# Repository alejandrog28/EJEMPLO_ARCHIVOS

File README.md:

# EJEMPLO_ARCHIVOS
Este es un ejemplo de como subir archivos a este repositorio remoto.

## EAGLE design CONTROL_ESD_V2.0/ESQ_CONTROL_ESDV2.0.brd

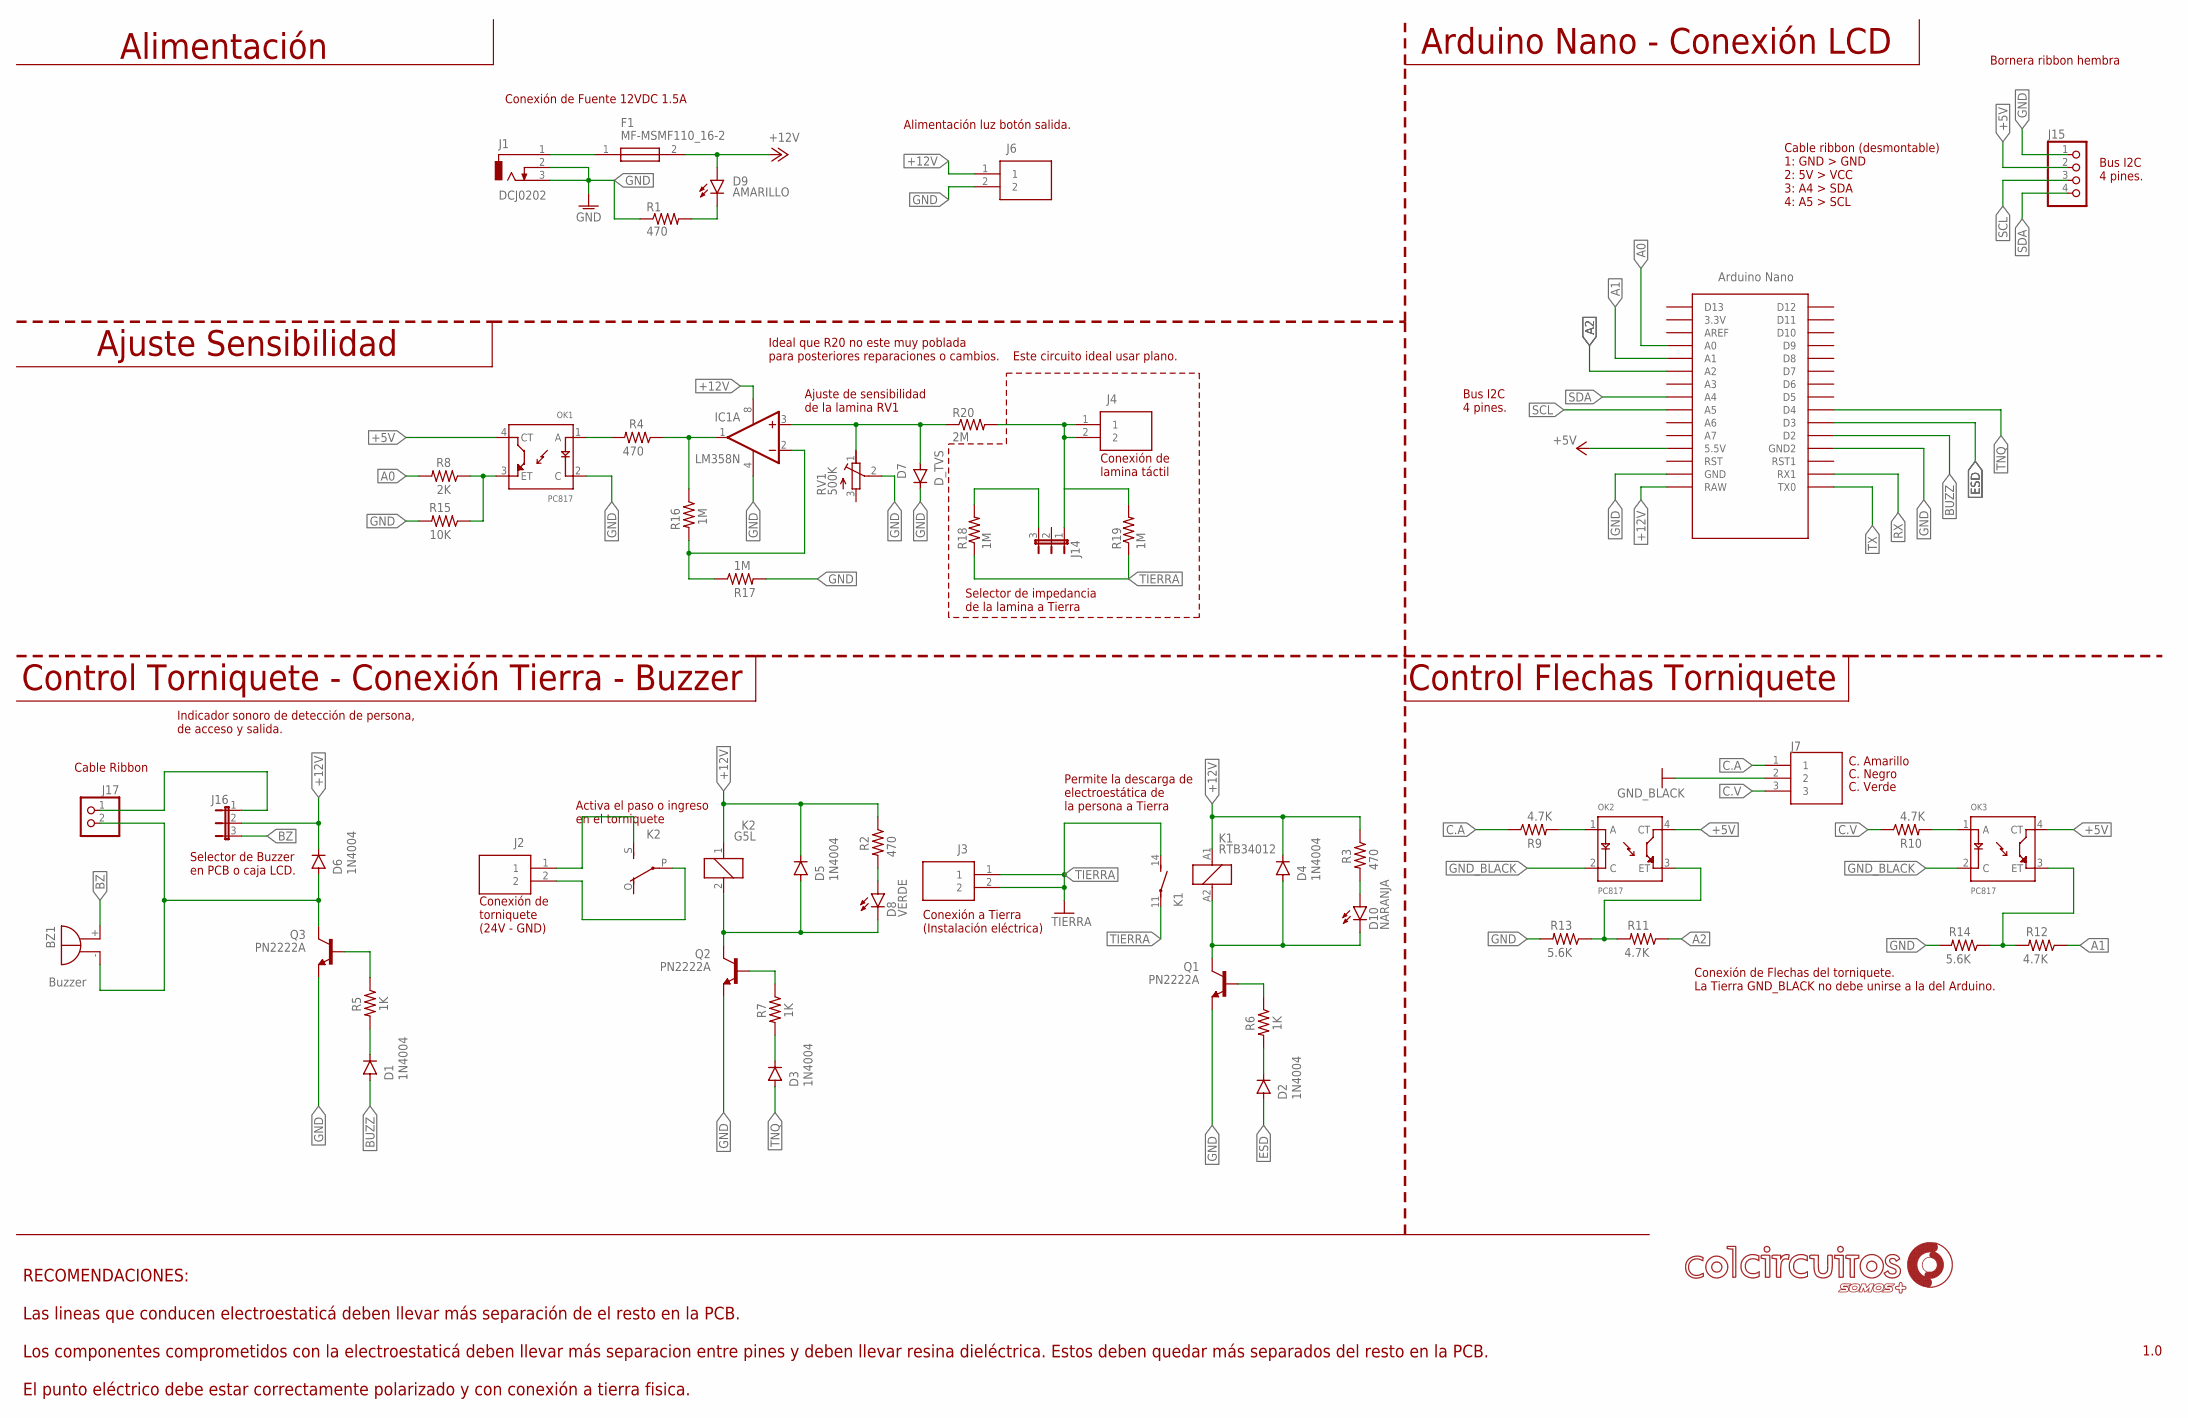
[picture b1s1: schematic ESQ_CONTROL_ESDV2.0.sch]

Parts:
BZ1: Buzzer; EB2209A
D1, D2, D3, D4, D5, D6: 1N4004; DO41-10
D7: D_TVS; DO214AC
D8: VERDE; LED5MM
D9: AMARILLO; LED5MM
D10: NARANJA; LED5MM
F1: MF-MSMF110_16-2; FUSC4632X85N
IC1: LM358N; DIL08
J1: DCJ0202
J2, J3, J4, J6: 20020107-H021A01LF; SHDR2W100P0X508_1X2_1216X850X1
J7: 691311500103; SHDR3W100P0X508_1X3_1724X850X1
J14, J16: JP2E; JP2
J15: PINHD-1X4; 1X04
J17: PINHD-1X2; 1X02
K1: RTB34012; RT-N/O12A3.5
K2: G5L; G5LE
OK1, OK2, OK3: PC817; SOT254P975X400-4N
Q1, Q2, Q3: PN2222A; TO92
R1, R2, R3, R4: 470; R0805
R5, R6, R7: 1K; R0805
R8: 2K; R0805
R9, R10, R11, R12: 4.7K; R0805
R13, R14: 5.6K; R0805
R15: 10K; R0805
R16, R17: 1M; R0805
R18, R19: 1M; R1210
R20: 2M; R1210
RV1: 500K; RTRIMT93YA
U$1: NANO

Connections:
+5V: J15.2, OK1.4 (CT), OK2.4 (CT), OK3.4 (CT), U$1.5V (5.5V)
+12V: D4.C, D5.C, D6.C, D9.A, F1.2, IC1.8 (V+), J6.1, J16.2, K1.A1 (1), K2.1, R2.1, R3.1, U$1.RAW
A0: R8.2, U$1.A0
A1: R12.1, U$1.A1
A2: R11.1, U$1.A2
BUZZ: D1.A, U$1.D2
BZ: BZ1.+, J16.3
C.A: J7.1, R9.1
C.V: J7.3, R10.1
ESD: D2.A, U$1.D3
GND: D7.C, IC1.4 (V-), J1.2, J1.3, J6.2, J15.1, OK1.2 (C), Q1.1 (E), Q2.1 (E), Q3.1 (E), R1.1, R13.2, R14.2, R15.2, R17.2, RV1.2 (S), U$1.GND, U$1.GND1 (GND2)
GND_BLACK: J7.2, OK2.2 (C), OK3.2 (C)
unnamed: OK1.3 (ET), R8.1, R15.1
unnamed: OK1.1 (A), R4.2
unnamed: IC1.2 (-IN), R16.2, R17.1
unnamed: IC1.1 (OUT), R4.1, R16.1
unnamed: D7.A, IC1.3 (+IN), R20.1, RV1.1 (E)
unnamed: J14.3, R18.2
unnamed: BZ1.-, D6.A, J17.2, Q3.3 (C)
unnamed: F1.1, J1.1
unnamed: J16.1, J17.1
unnamed: D9.K (C), R1.2
unnamed: J2.1, K2.S
unnamed: D5.A, D8.K (C), K2.2, Q2.3 (C)
unnamed: J2.2, K2.P
unnamed: D8.A, R2.2
unnamed: D3.C, R7.2
unnamed: Q2.2 (B), R7.1
unnamed: D4.A, D10.K (C), K1.A2 (2), Q1.3 (C)
unnamed: D2.C, R6.2
unnamed: Q1.2 (B), R6.1
unnamed: OK2.1 (A), R9.2
unnamed: OK2.3 (ET), R11.2, R13.1
unnamed: OK3.3 (ET), R12.2, R14.1
unnamed: D10.A, R3.2
unnamed: OK3.1 (A), R10.2
unnamed: J4.1, J4.2, J14.1, R19.2, R20.2
unnamed: Q3.2 (B), R5.1
unnamed: D1.C, R5.2
RX: U$1.RX1
SCL: J15.3, U$1.A5
SDA: J15.4, U$1.A4
TIERRA: J3.1, J3.2, K1.11, K1.14 (S), R18.1, R19.1
TNQ: D3.A, U$1.D4
TX: U$1.TX0

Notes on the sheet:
Ajuste de sensibilidad de la lamina RV1
Conexión de lamina táctil
Selector de impedancia de la lamina a Tierra
Activa el paso o ingreso en el torniquete
Conexión de torniquete (24V - GND)
Permite la descarga de electroestática de la persona a Tierra
Conexión a Tierra (Instalación eléctrica)
C. Amarillo
C. Negro
C. Verde
Conexión de Flechas del torniquete. La Tierra GND_BLACK no debe unirse a la del Arduino.
Alimentación
Ajuste Sensibilidad
Control Flechas Torniquete
Control Torniquete - Conexión Tierra - Buzzer
Arduino Nano - Conexión LCD
Cable ribbon (desmontable) 1: GND > GND 2: 5V > VCC 3: A4 > SDA 4: A5 > SCL
Bus I2C 4 pines.
RECOMENDACIONES: Las lineas que conducen electroestaticá deben llevar más separación de el resto en la PCB. Los componentes comprometidos con la electroestaticá deben llevar más separacion entre pines y deben llevar resina dieléctrica. Estos deben quedar más separados del resto en la PCB. El punto 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
1.0
Alimentación luz botón salida.
Este circuito ideal usar plano.
Ideal que R20 no este muy poblada para posteriores reparaciones o cambios.
Bornera ribbon hembra
Indicador sonoro de detección de persona, de acceso y salida.
Conexión de Fuente 12VDC 1.5A
Selector de Buzzer en PCB o caja LCD.
Cable Ribbon

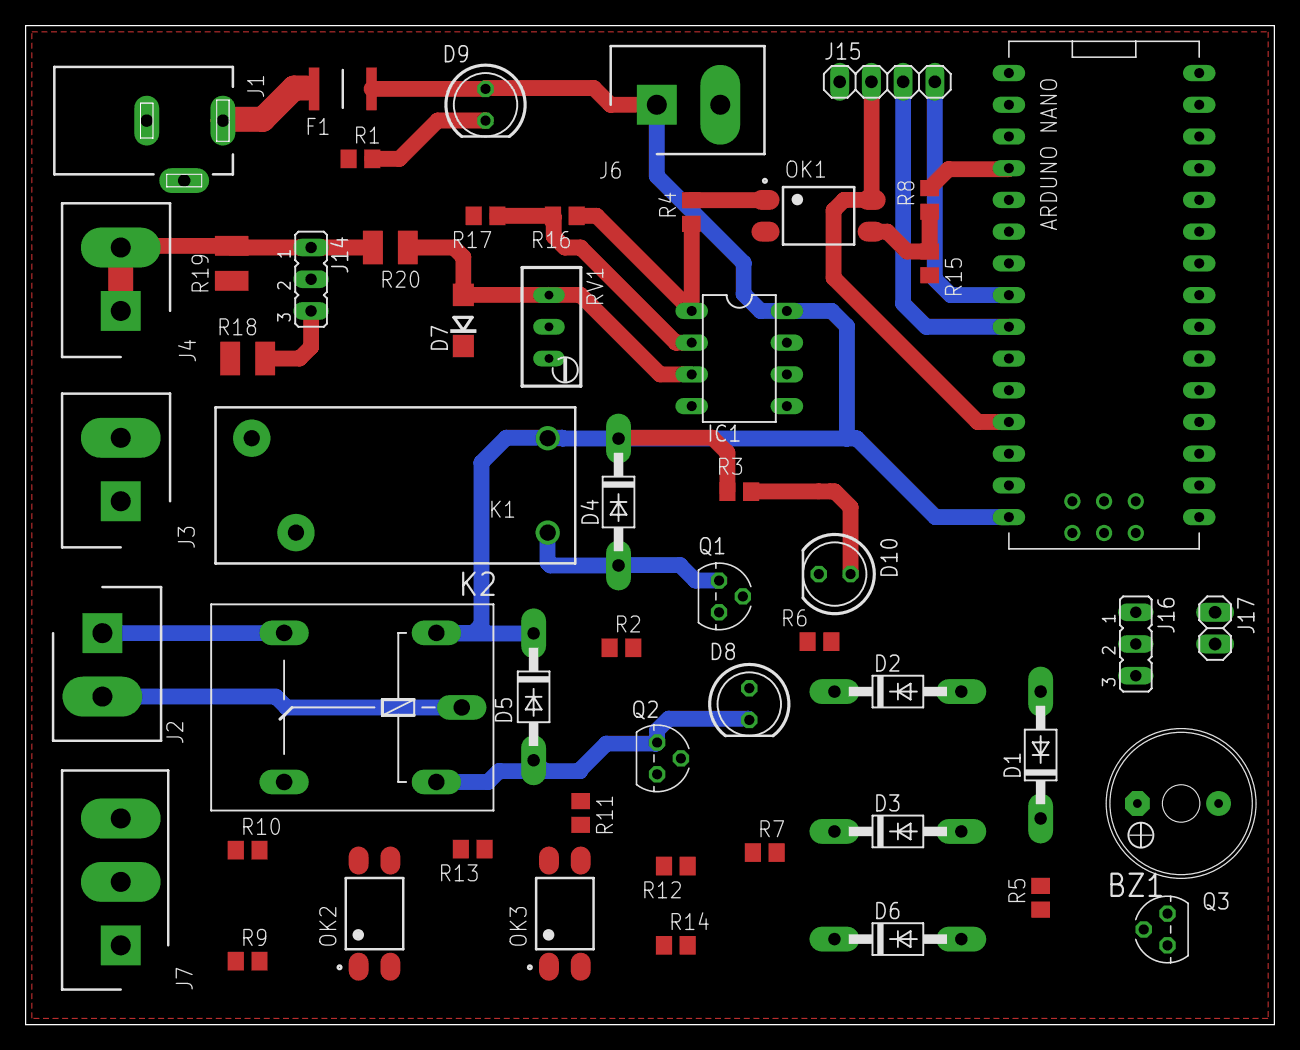
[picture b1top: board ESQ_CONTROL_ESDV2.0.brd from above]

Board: 2 copper layers, 100.0 x 80.0 mm, 53 parts (0 on the bottom side), 43 nets.

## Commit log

2024-01-11 Se agregan archivos EAGLE.
    Estos archivos son extension .BDR .SCH
